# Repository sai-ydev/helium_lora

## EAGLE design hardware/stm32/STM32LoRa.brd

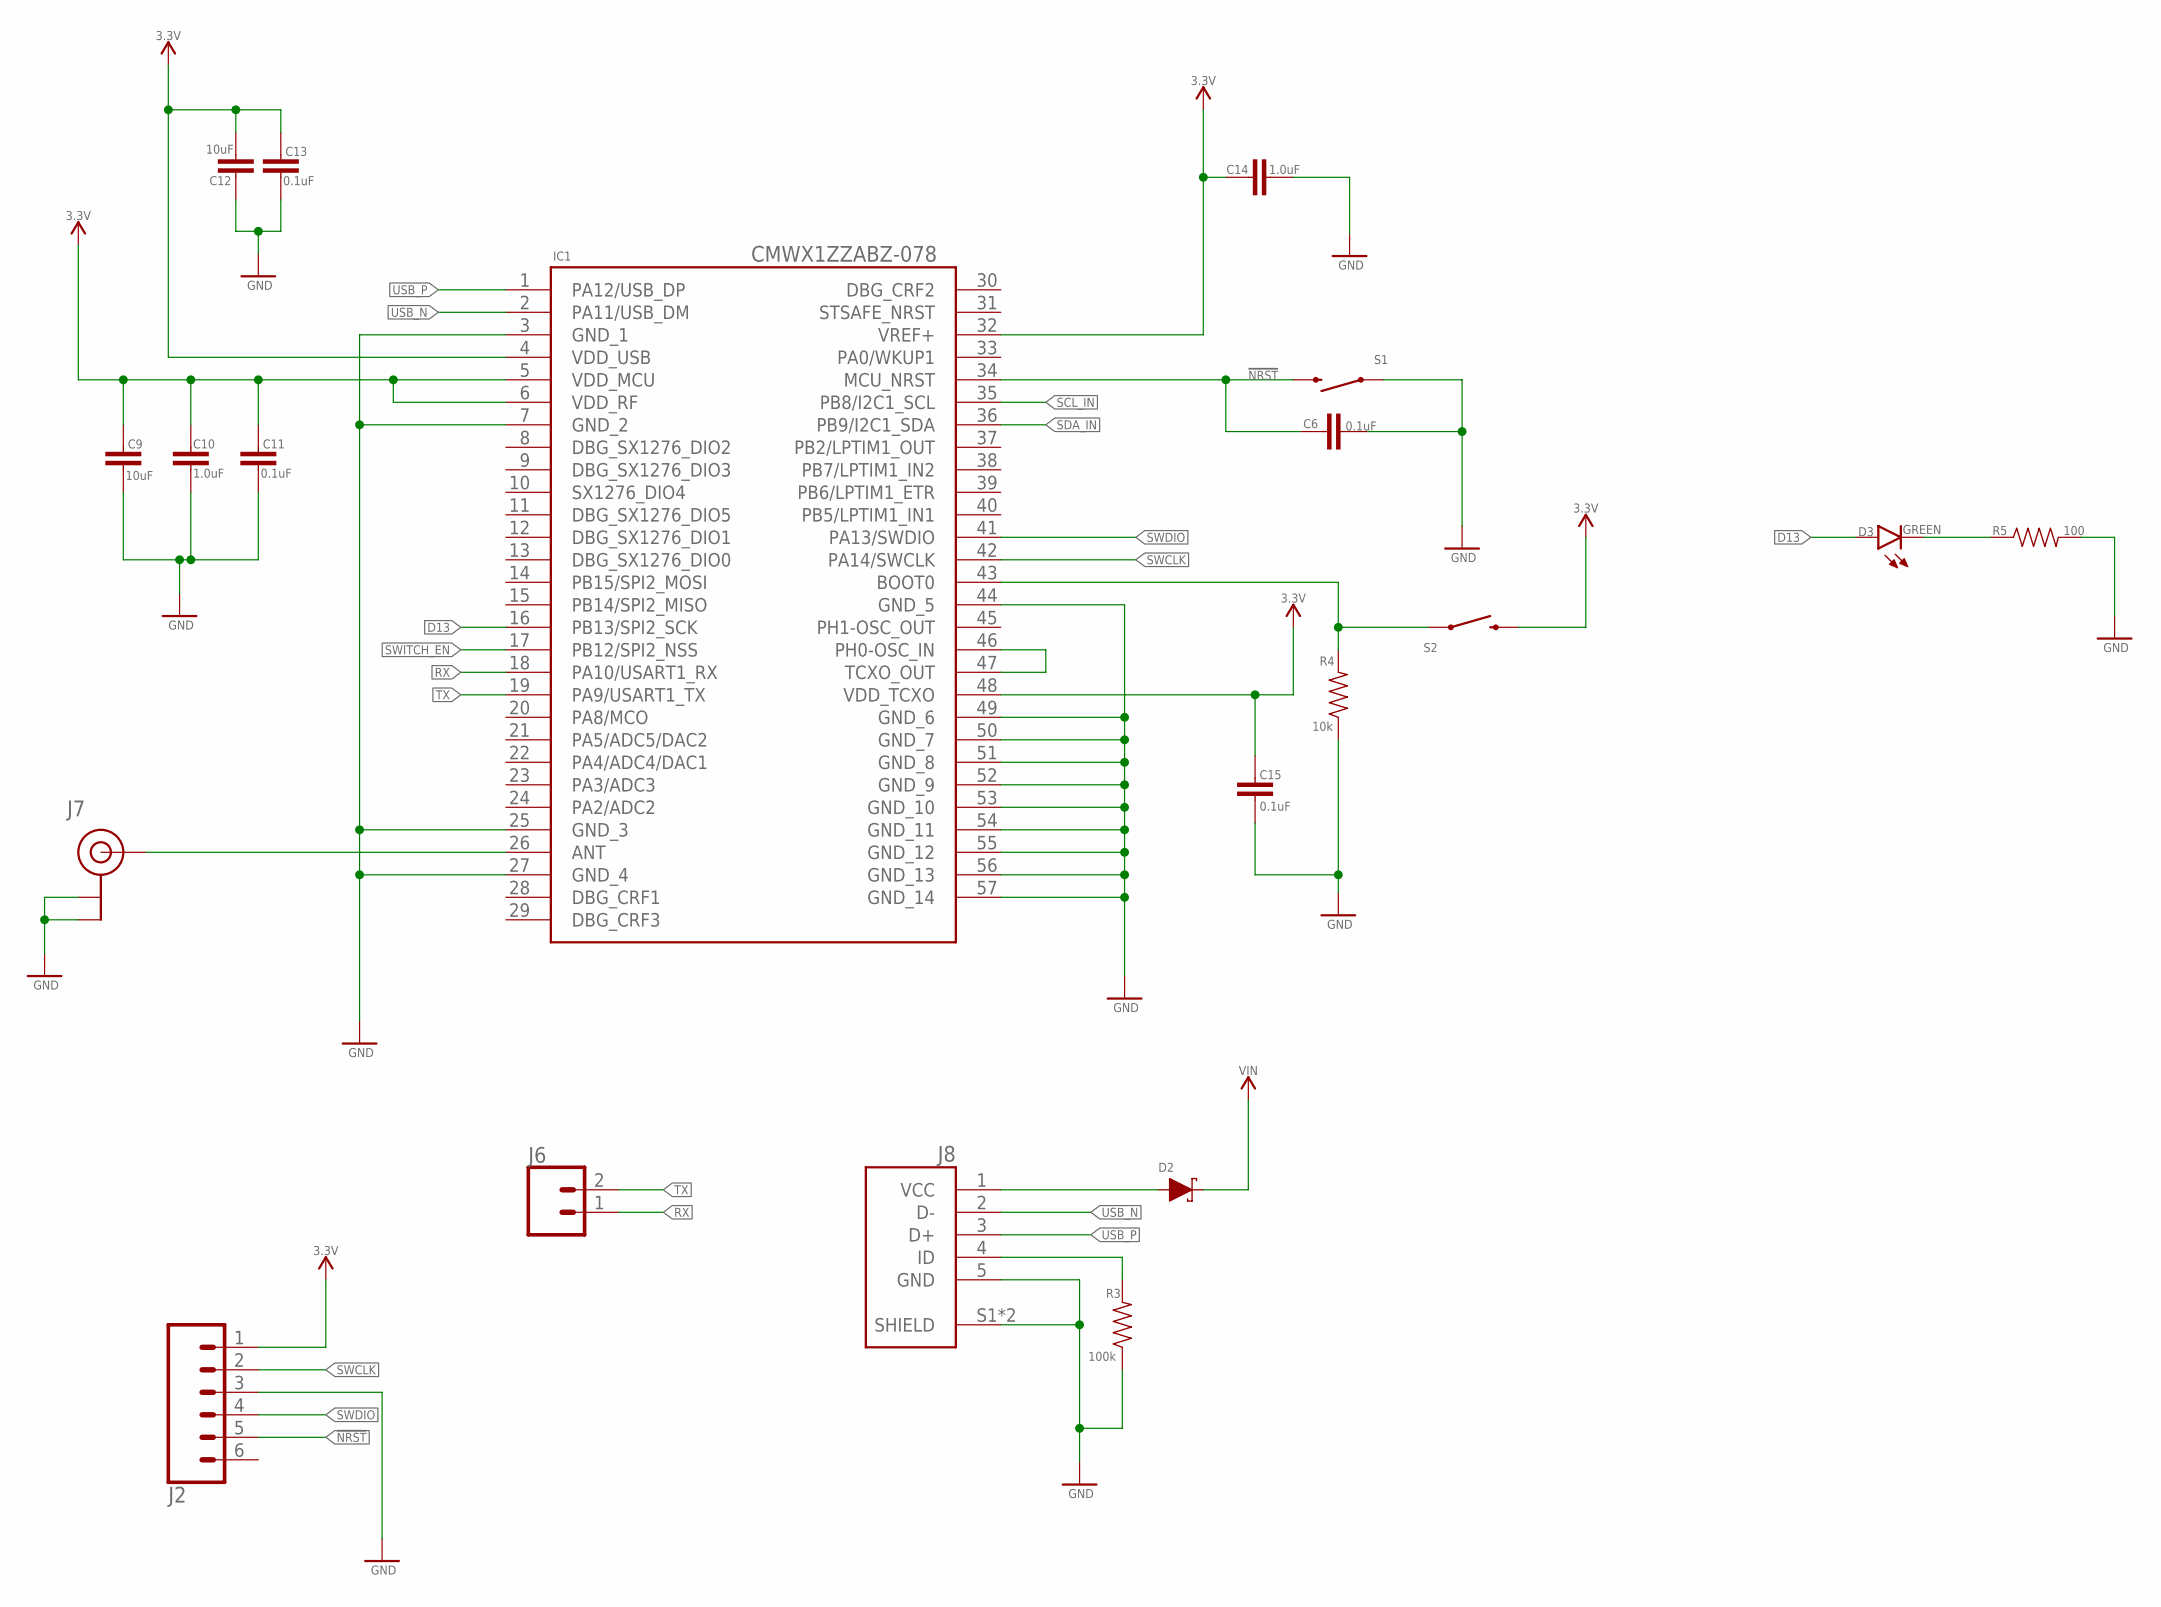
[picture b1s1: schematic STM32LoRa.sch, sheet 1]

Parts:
C6, C11, C13, C15: 0.1uF; 0603
C9, C12: 10uF; 0603
C10, C14: 1.0uF; 0603
D2: 120mA/40V/370mV; SOD-523
D3: GREEN; LED-0603
IC1: CMWX1ZZABZ-078
J2: CONN_06LONGPADS; 1X06_LONGPADS
J6: CONN_02; 1X02
J7: U.FL
J8: USB3131-30-0230-A_REVB; GCT_USB3131-30-0230-A_REVB
R3: 100k; 0603
R4: 10k; 0603
R5: 100; 0603
S1, S2: MOMENTARY-SWITCH-SPST-SMD-4.6X2.8MM; TACTILE_SWITCH_SMD_4.6X2.8MM

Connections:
3.3V: C9.1, C10.1, C11.1, C12.2, C13.1, C14.1, C15.2, IC1.4 (VDD_USB), IC1.5 (VDD_MCU), IC1.6 (VDD_RF), IC1.32 (VREF+), IC1.48 (VDD_TCXO), J2.1, S2.3 (2), S2.4 (2); also elsewhere on the board
!NRST: C6.1, IC1.34 (MCU_NRST), J2.5, S1.3 (2), S1.4 (2)
D13: D3.A, IC1.16 (PB13/SPI2_SCK)
GND: C6.2, C9.2, C10.2, C11.2, C12.1, C13.2, C14.2, C15.1, IC1.3 (GND_1), IC1.7 (GND_2), IC1.25 (GND_3), IC1.27 (GND_4), IC1.44 (GND_5), IC1.49 (GND_6), IC1.50 (GND_7), IC1.51 (GND_8), IC1.52 (GND_9), IC1.53 (GND_10), IC1.54 (GND_11), IC1.55 (GND_12), IC1.56 (GND_13), IC1.57 (GND_14), J2.3, J7.1 (GND), J7.2 (GND), J8.5 (GND), J8.S1 (SHIELD), J8.S2 (SHIELD), R3.1, R4.1, R5.2, S1.1, S1.2 (1); also elsewhere on the board
unnamed: IC1.43 (BOOT0), R4.2, S2.1, S2.2 (1)
unnamed: IC1.46 (PH0-OSC_IN), IC1.47 (TCXO_OUT)
unnamed: IC1.26 (ANT), J7.FEED (SIGNAL)
unnamed: D3.C, R5.1
unnamed: J8.4 (ID), R3.2
unnamed: D2.A, J8.1 (VCC)
RX: IC1.18 (PA10/USART1_RX), J6.1
SCL_IN: IC1.35 (PB8/I2C1_SCL); also elsewhere on the board
SDA_IN: IC1.36 (PB9/I2C1_SDA); also elsewhere on the board
SWCLK: IC1.42 (PA14/SWCLK), J2.2
SWDIO: IC1.41 (PA13/SWDIO), J2.4
SWITCH_EN: IC1.17 (PB12/SPI2_NSS); also elsewhere on the board
TX: IC1.19 (PA9/USART1_TX), J6.2
USB_N: IC1.2 (PA11/USB_DM), J8.2 (D-)
USB_P: IC1.1 (PA12/USB_DP), J8.3 (D+)
VIN: D2.C; also elsewhere on the board

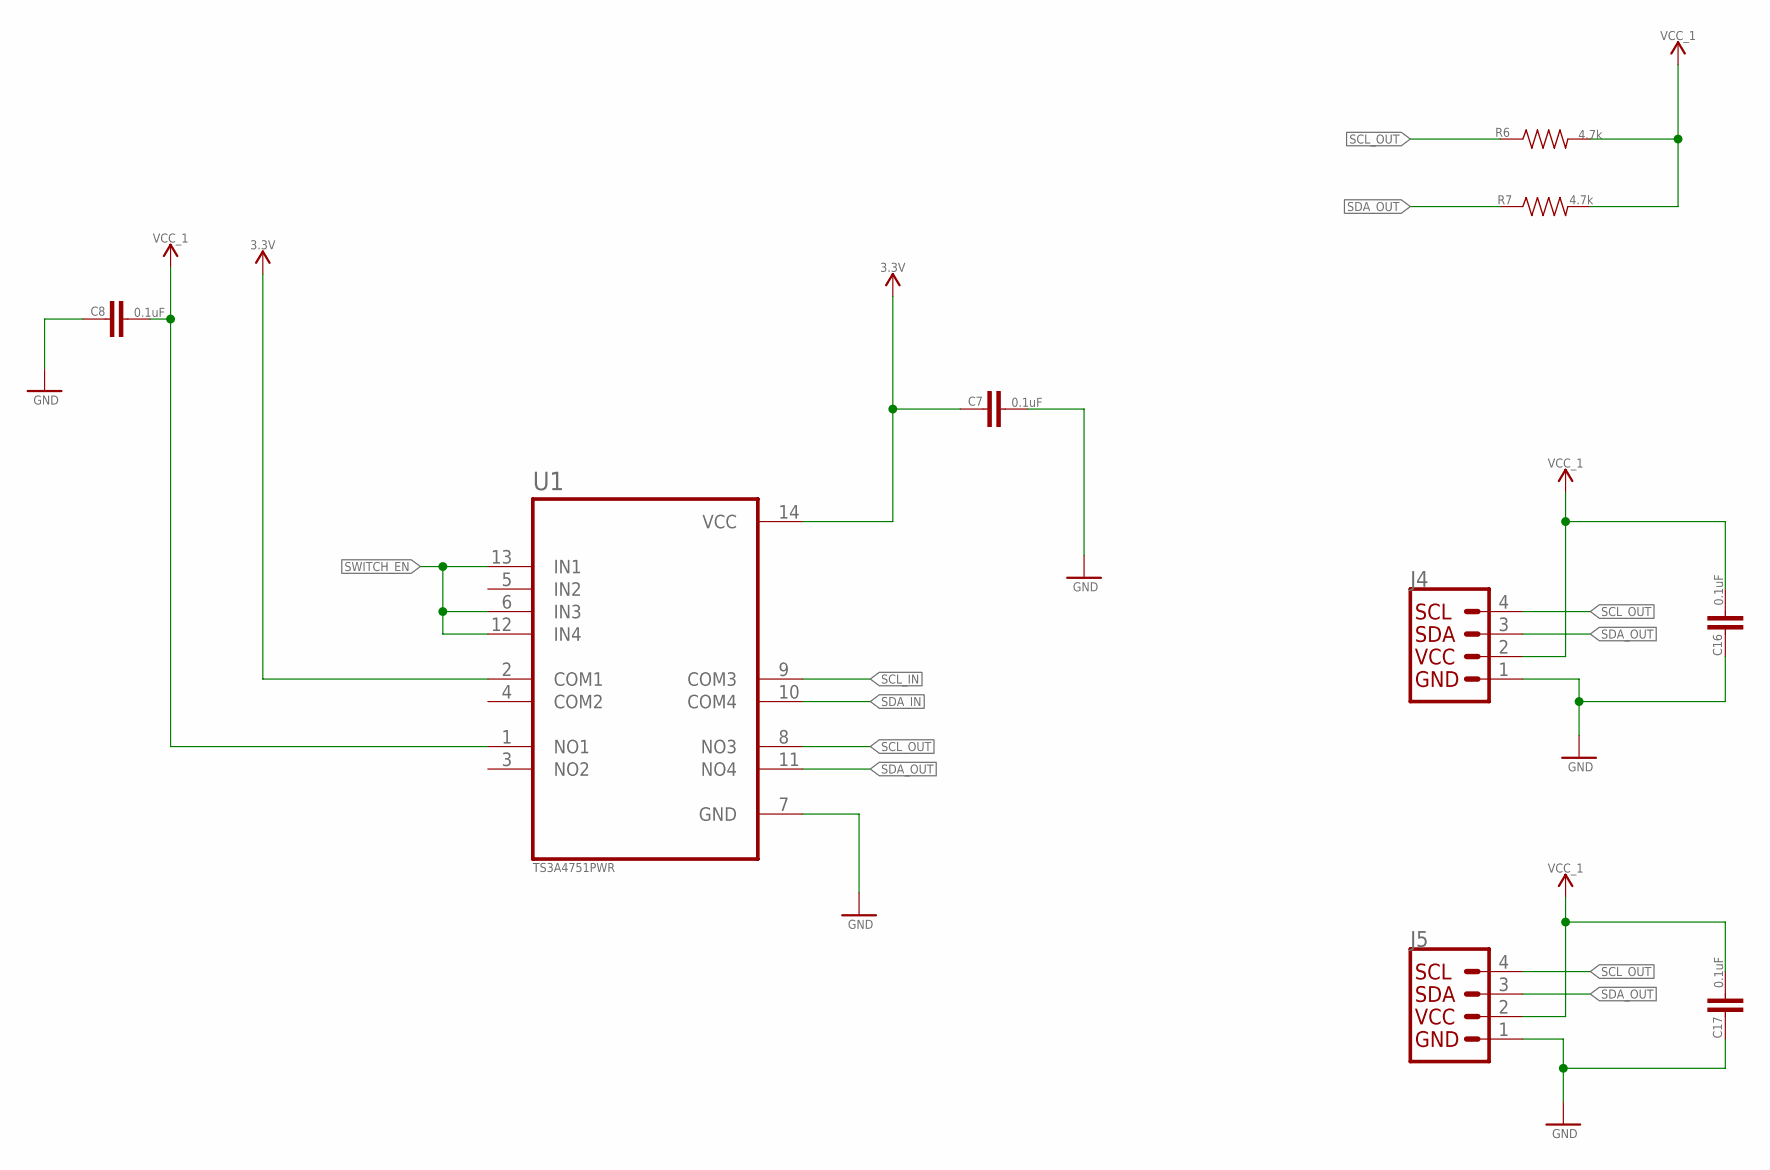
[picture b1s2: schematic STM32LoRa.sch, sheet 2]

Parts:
C7, C8, C16, C17: 0.1uF; 0603
J4: Qwiic Right Angle; 1X04_1MM_RA
J5: I2C_STANDARD; 1X04
R6, R7: 4.7k; 0603
U1: TS3A4751PWR; SOP65P640X120-14N

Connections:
3.3V: C7.1, U1.2 (COM1), U1.14 (VCC); also elsewhere on the board
GND: C7.2, C8.1, C16.1, C17.1, J4.1, J5.1, U1.7 (GND); also elsewhere on the board
SCL_IN: U1.9 (COM3); also elsewhere on the board
SCL_OUT: J4.4, J5.4, R6.1, U1.8 (NO3)
SDA_IN: U1.10 (COM4); also elsewhere on the board
SDA_OUT: J4.3, J5.3, R7.1, U1.11 (NO4)
SWITCH_EN: U1.6 (IN3), U1.12 (IN4), U1.13 (IN1); also elsewhere on the board
VCC_1: C8.2, C16.2, C17.2, J4.2, J5.2, R6.2, R7.2, U1.1 (NO1)

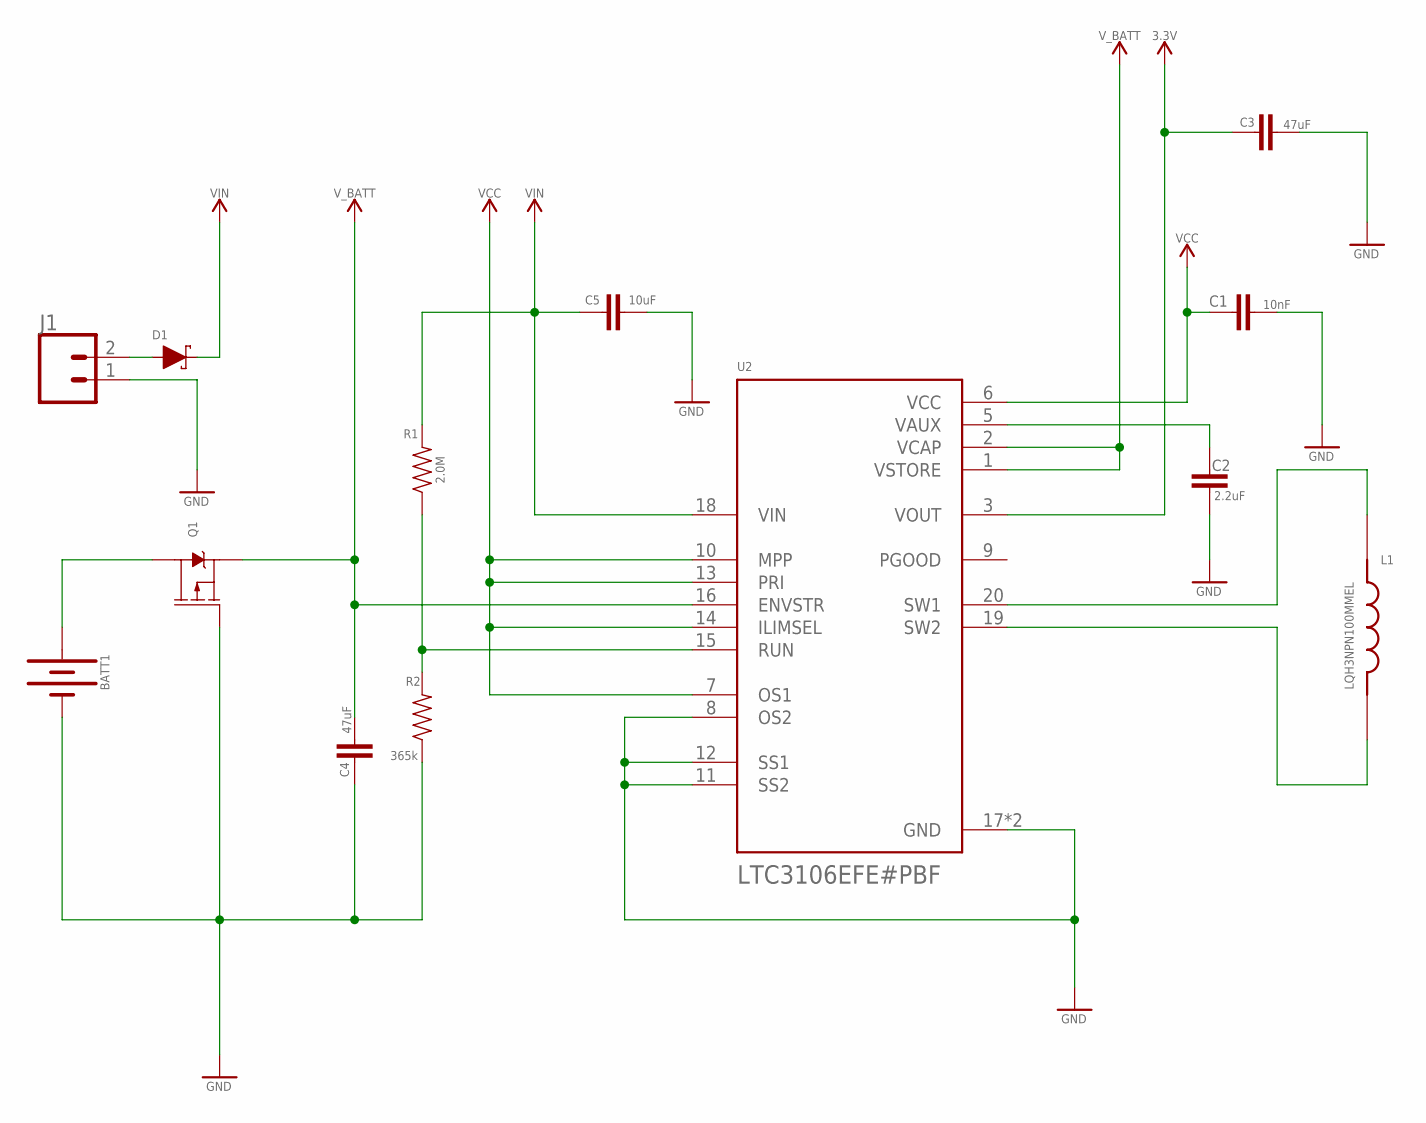
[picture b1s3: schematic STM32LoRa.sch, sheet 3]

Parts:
BATT1: KEYSTONE_54KEYSTONE_2; KEYSTONE_V2
C1: 10nF; 0603
C2: 2.2uF; 0603
C3, C4: 47uF; 0603
C5: 10uF; 0603
D1: 120mA/40V/370mV; SOD-523
J1: CONN_023.5MM; SCREWTERMINAL-3.5MM-2
L1: LQH3NPN100MMEL; IND_LQH3NPN100MMEL
Q1: 2.5A/30V/105mΩ; SOT23-3
R1: 2.0M; 0603
R2: 365k; 0603
U2: LTC3106EFE#PBF; SOP65P640X120-21N

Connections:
3.3V: C3.1, U2.3 (VOUT); also elsewhere on the board
GND: BATT1.P$4 (-), BATT1.P$5 (-), BATT1.P$6 (-), C1.2, C2.2, C3.2, C4.1, C5.2, J1.1, Q1.1 (G), R2.1, U2.8 (OS2), U2.11 (SS2), U2.12 (SS1), U2.17 (GND), U2.21 (GND); also elsewhere on the board
unnamed: L1.1, U2.20 (SW1)
unnamed: L1.2, U2.19 (SW2)
unnamed: C2.1, U2.5 (VAUX)
unnamed: BATT1.P$1 (+), BATT1.P$2 (+), BATT1.P$3 (+), Q1.3 (D)
unnamed: R1.1, R2.2, U2.15 (RUN)
unnamed: D1.A, J1.2
VCC: C1.1, U2.6 (VCC), U2.7 (OS1), U2.10 (MPP), U2.13 (PRI), U2.14 (ILIMSEL)
VIN: C5.1, D1.C, R1.2, U2.18 (VIN); also elsewhere on the board
V_BATT: C4.2, Q1.2 (S), U2.1 (VSTORE), U2.2 (VCAP), U2.16 (ENVSTR)

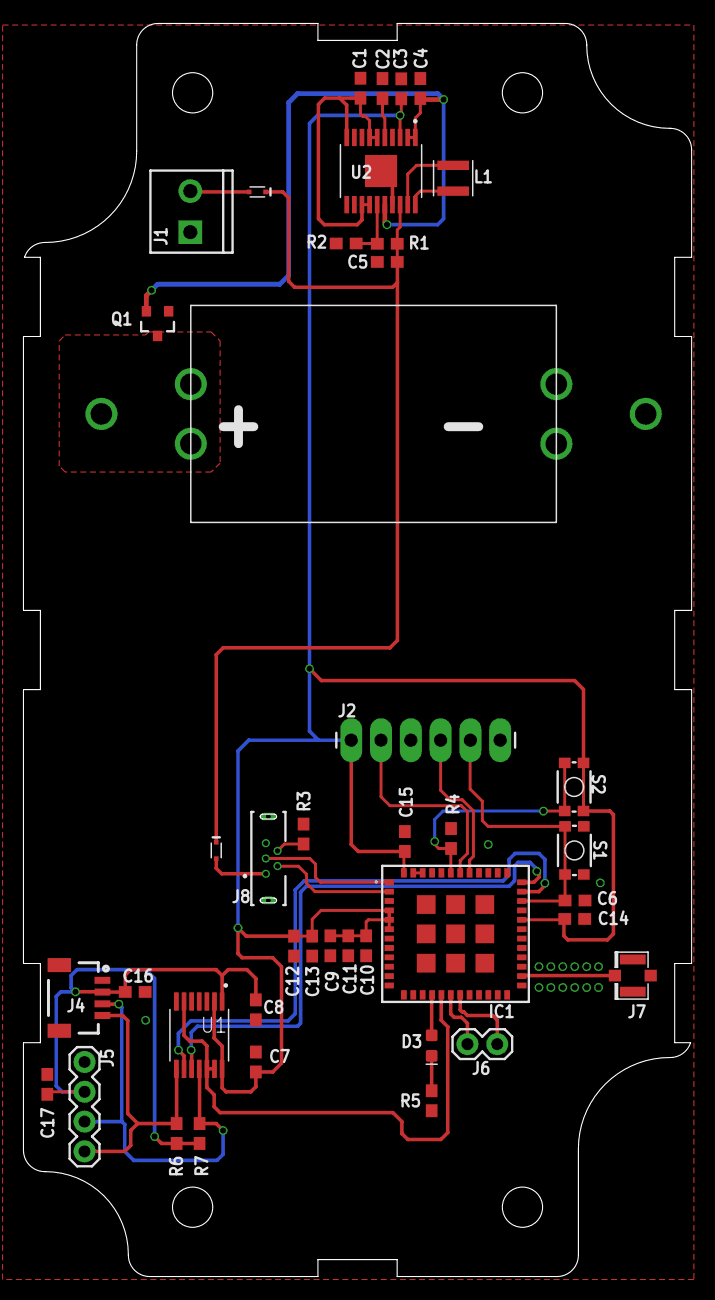
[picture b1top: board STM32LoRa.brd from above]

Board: 2 copper layers, 57.0 x 106.8 mm, 42 parts (0 on the bottom side), 31 nets.

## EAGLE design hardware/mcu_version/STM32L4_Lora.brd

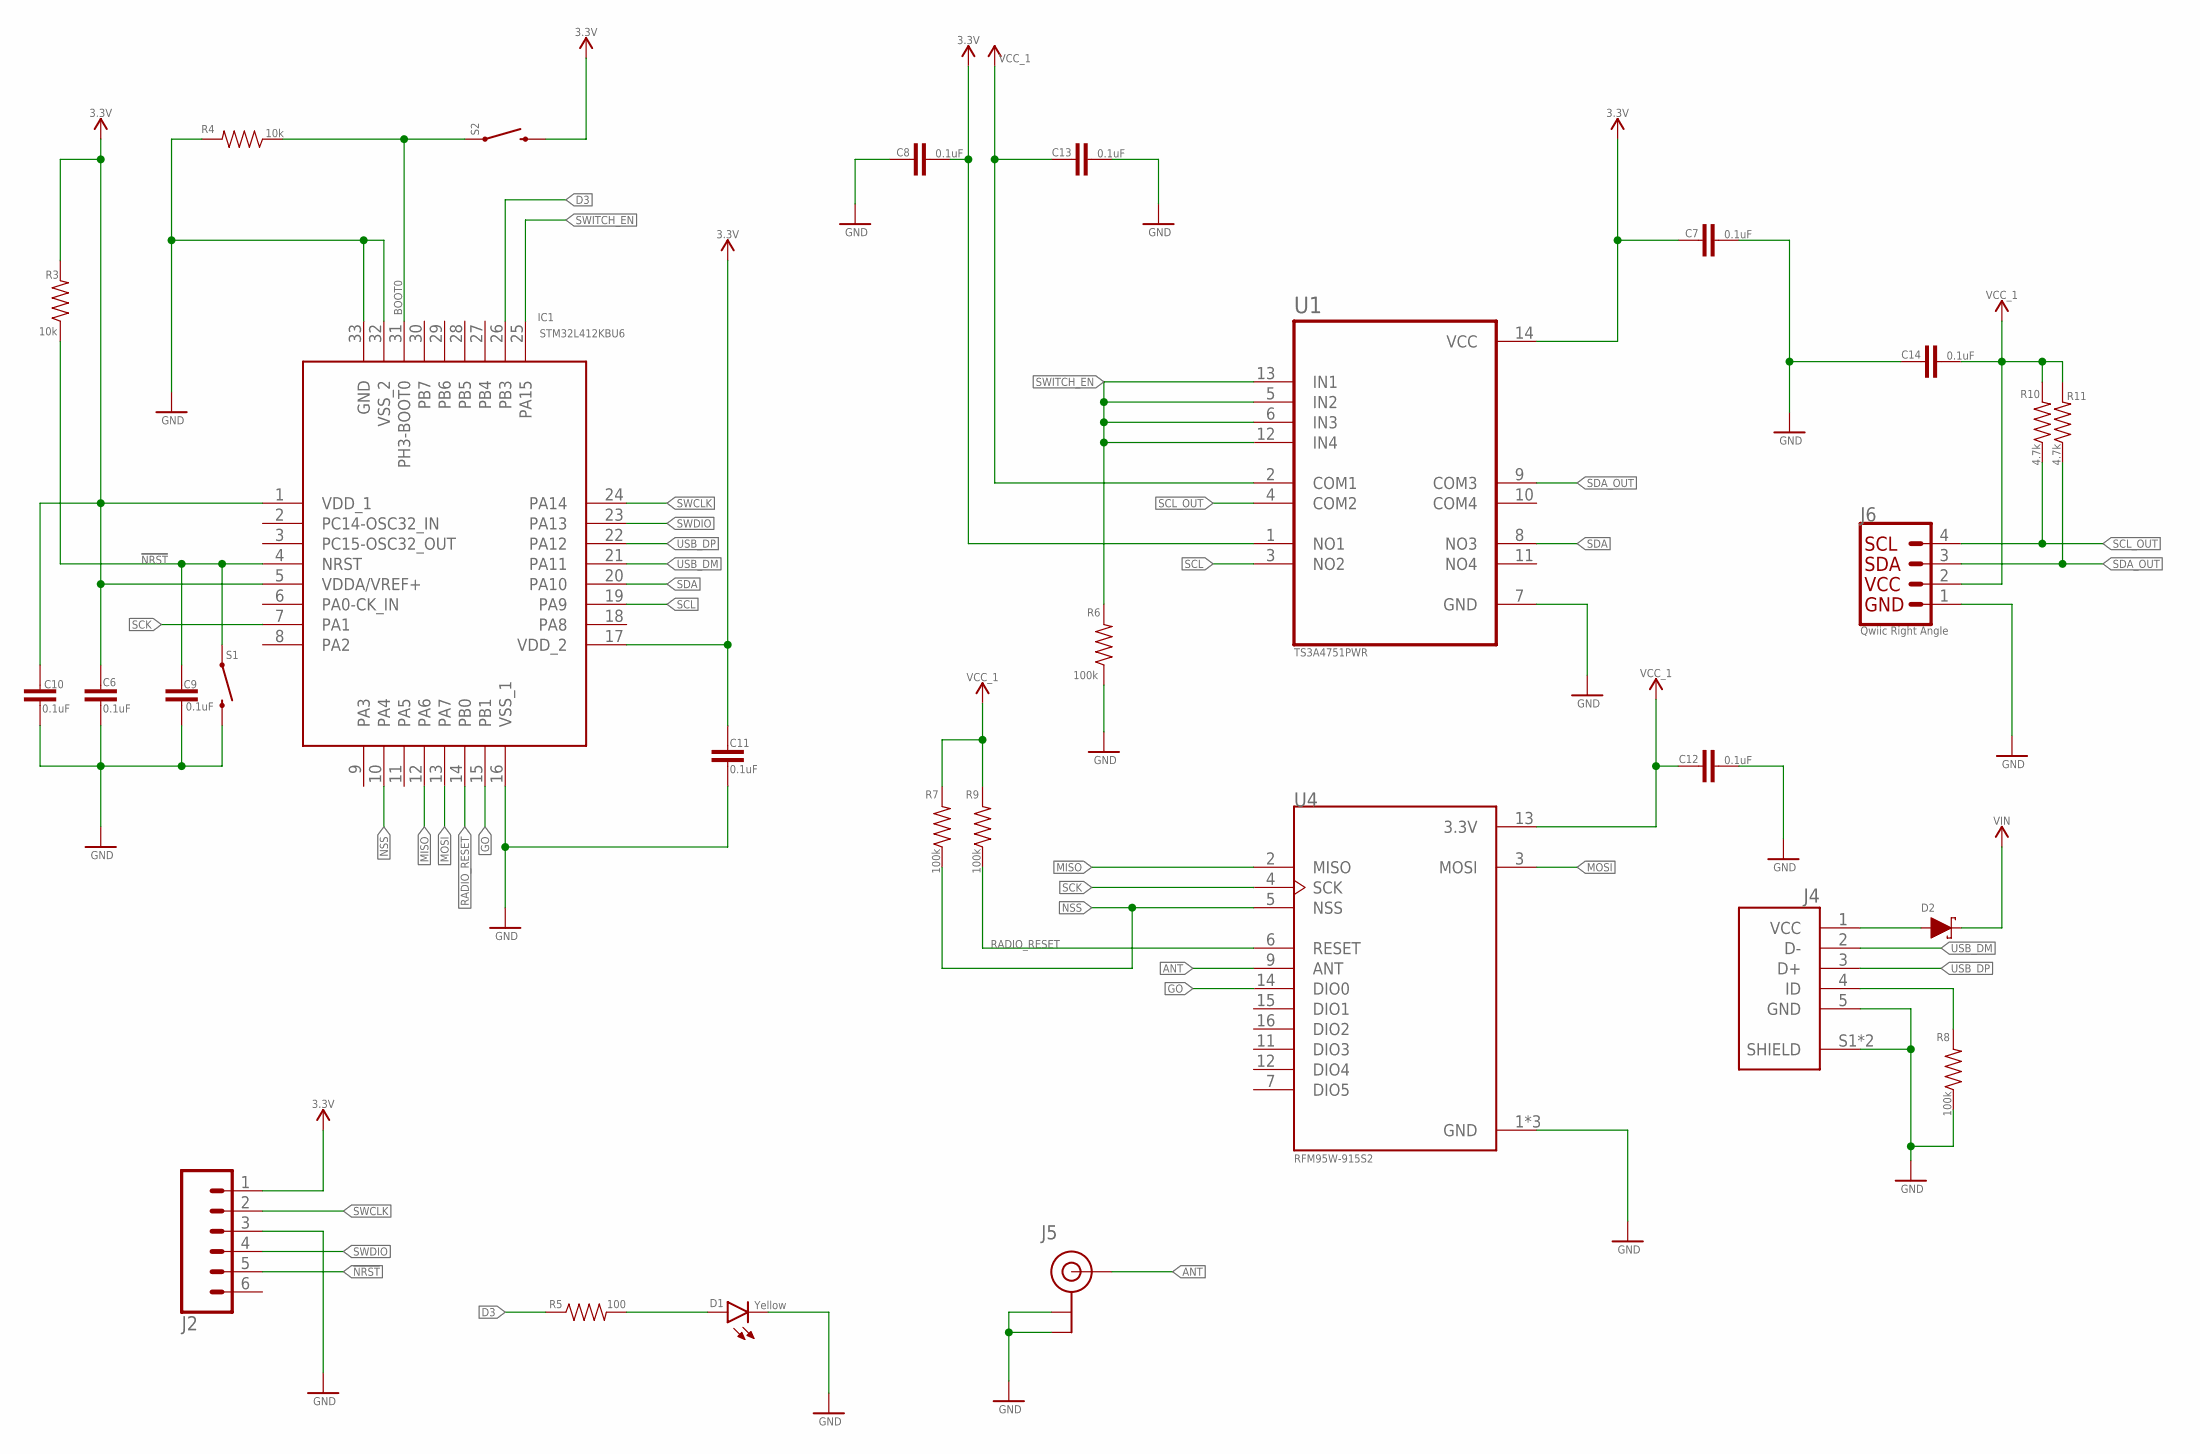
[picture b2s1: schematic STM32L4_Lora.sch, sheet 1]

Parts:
C6, C7, C8, C9, C10, C11, C12, C13, C14: 0.1uF; 0603
D1: Yellow; LED-0603
D2: 120mA/40V/370mV; SOD-523
IC1: STM32L412KBU6; QFN50P500X500X60-33N
J2: CONN_06LOCK_LONGPADS; 1X06_LOCK_LONGPADS
J4: USB3131-30-0230-A_REVB; GCT_USB3131-30-0230-A_REVB
J5: U.FL
J6: Qwiic Right Angle; 1X04_1MM_RA
R3, R4: 10k; 0603
R5: 100; 0603
R6, R7, R8, R9: 100k; 0603
R10, R11: 4.7k; 0603
S1, S2: MOMENTARY-SWITCH-SPST-SMD-4.6X2.8MM; TACTILE_SWITCH_SMD_4.6X2.8MM
U1: TS3A4751PWR; SOP65P640X120-14N
U4: RFM95W-915S2; XCVR_RFM95W-915S2

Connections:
3.3V: C6.1, C7.1, C8.2, C10.1, C11.1, IC1.1 (VDD_1), IC1.5 (VDDA/VREF+), IC1.17 (VDD_2), J2.1, R3.2, S2.3 (2), S2.4 (2), U1.1 (NO1), U1.14 (VCC); also elsewhere on the board
!NRST: C9.1, IC1.4 (NRST), J2.5, R3.1, S1.1, S1.2 (1)
ANT: J5.FEED (SIGNAL), U4.9 (ANT)
BOOT0: IC1.31 (PH3-BOOT0), R4.1, S2.1, S2.2 (1)
D3: IC1.26 (PB3), R5.1
GND: C6.2, C7.2, C8.1, C9.2, C10.2, C11.2, C12.2, C13.2, C14.1, D1.C, IC1.16 (VSS_1), IC1.32 (VSS_2), IC1.33 (GND), J2.3, J4.5 (GND), J4.S1 (SHIELD), J4.S2 (SHIELD), J5.1 (GND), J5.2 (GND), J6.1, R4.2, R6.1, R8.1, S1.3 (2), S1.4 (2), U1.7 (GND), U4.1 (GND), U4.8 (GND), U4.10 (GND); also elsewhere on the board
GO: IC1.15 (PB1), U4.14 (DIO0)
MISO: IC1.12 (PA6), U4.2 (MISO)
MOSI: IC1.13 (PA7), U4.3 (MOSI)
unnamed: D1.A, R5.2
unnamed: J4.4 (ID), R8.2
unnamed: D2.A, J4.1 (VCC)
NSS: IC1.10 (PA4), R7.1, U4.5 (NSS)
RADIO_RESET: IC1.14 (PB0), R9.1, U4.6 (RESET)
SCK: IC1.7 (PA1), U4.4 (SCK)
SCL: IC1.19 (PA9), U1.3 (NO2)
SCL_OUT: J6.4, R10.1, U1.4 (COM2)
SDA: IC1.20 (PA10), U1.8 (NO3)
SDA_OUT: J6.3, R11.1, U1.9 (COM3)
SWCLK: IC1.24 (PA14), J2.2
SWDIO: IC1.23 (PA13), J2.4
SWITCH_EN: IC1.25 (PA15), R6.2, U1.5 (IN2), U1.6 (IN3), U1.12 (IN4), U1.13 (IN1)
USB_DM: IC1.21 (PA11), J4.2 (D-)
USB_DP: IC1.22 (PA12), J4.3 (D+)
VCC_1: C12.1, C13.1, C14.2, J6.2, R7.2, R9.2, R10.2, R11.2, U1.2 (COM1), U4.13 (3.3V)
VIN: D2.C; also elsewhere on the board

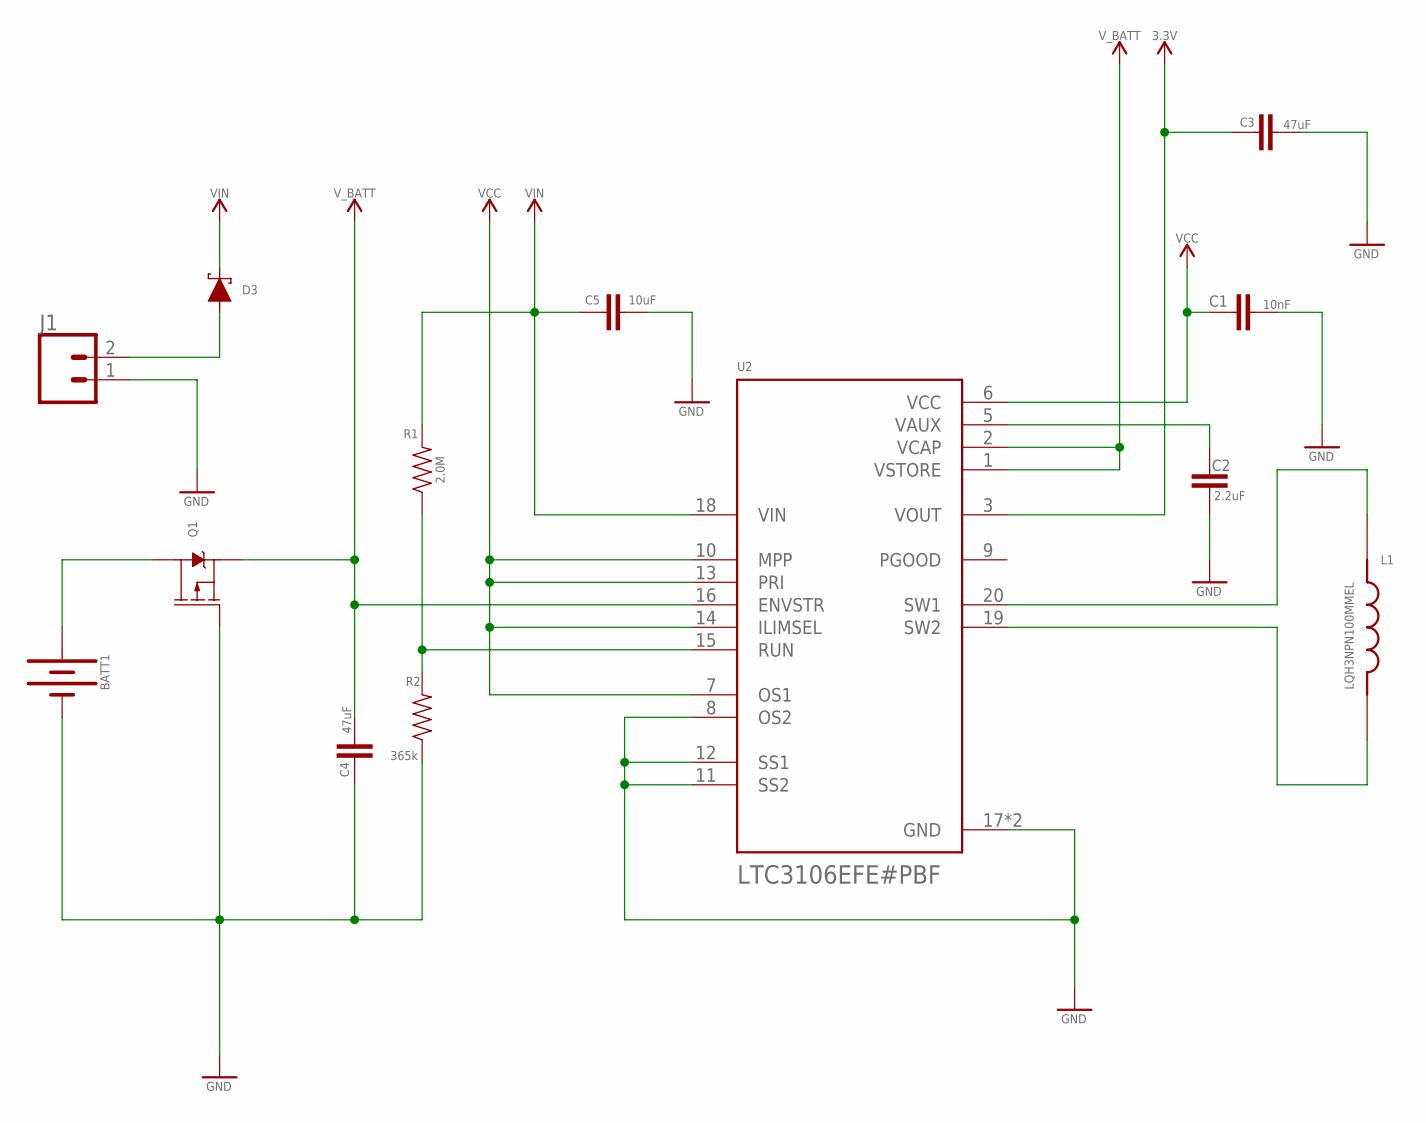
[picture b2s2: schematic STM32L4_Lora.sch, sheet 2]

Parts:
BATT1: KEYSTONE_54KEYSTONE_2; KEYSTONE_V2
C1: 10nF; 0603
C2: 2.2uF; 0603
C3, C4: 47uF; 0603
C5: 10uF; 0603
D3: 120mA/40V/370mV; SOD-523
J1: CONN_023.5MM; SCREWTERMINAL-3.5MM-2
L1: LQH3NPN100MMEL; IND_LQH3NPN100MMEL
Q1: 2.5A/30V/105mΩ; SOT23-3
R1: 2.0M; 0603
R2: 365k; 0603
U2: LTC3106EFE#PBF; SOP65P640X120-21N

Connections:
3.3V: C3.1, U2.3 (VOUT); also elsewhere on the board
GND: BATT1.P$4 (-), BATT1.P$5 (-), BATT1.P$6 (-), C1.2, C2.2, C3.2, C4.1, C5.2, J1.1, Q1.1 (G), R2.1, U2.8 (OS2), U2.11 (SS2), U2.12 (SS1), U2.17 (GND), U2.21 (GND); also elsewhere on the board
unnamed: L1.1, U2.20 (SW1)
unnamed: L1.2, U2.19 (SW2)
unnamed: C2.1, U2.5 (VAUX)
unnamed: BATT1.P$1 (+), BATT1.P$2 (+), BATT1.P$3 (+), Q1.3 (D)
unnamed: R1.1, R2.2, U2.15 (RUN)
unnamed: D3.A, J1.2
VCC: C1.1, U2.6 (VCC), U2.7 (OS1), U2.10 (MPP), U2.13 (PRI), U2.14 (ILIMSEL)
VIN: C5.1, D3.C, R1.2, U2.18 (VIN); also elsewhere on the board
V_BATT: C4.2, Q1.2 (S), U2.1 (VSTORE), U2.2 (VCAP), U2.16 (ENVSTR)

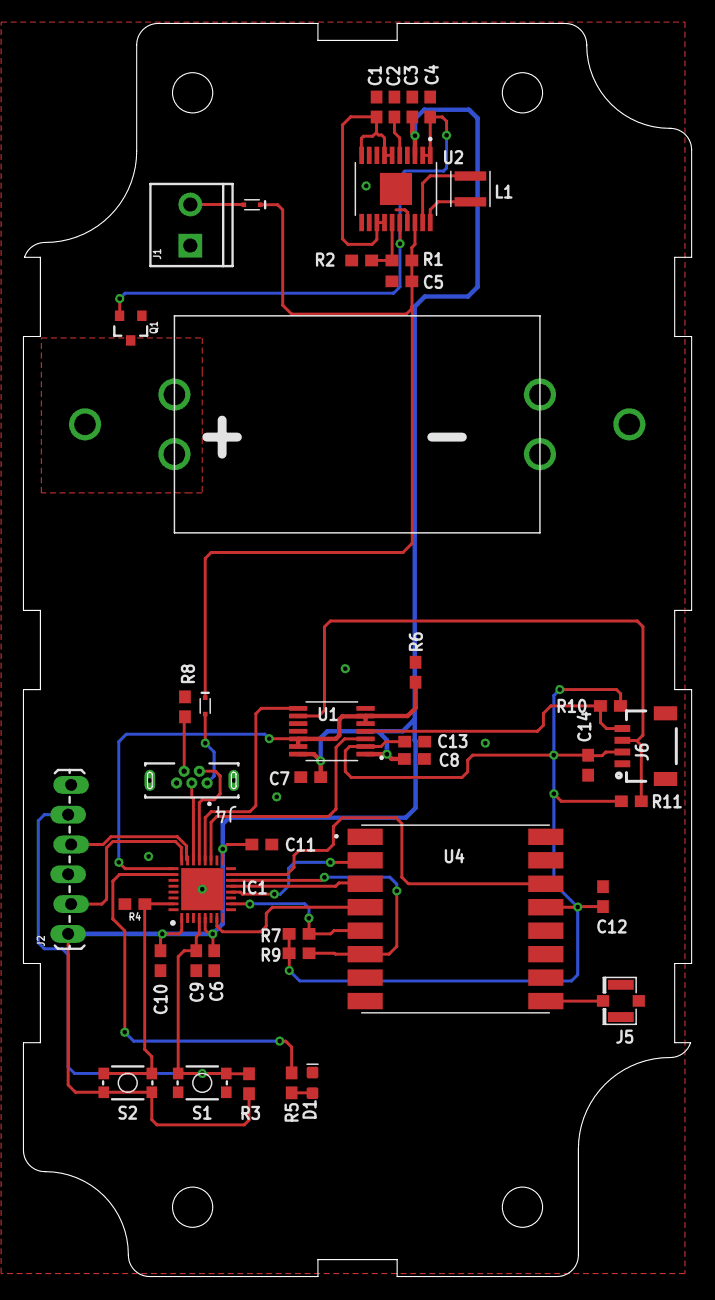
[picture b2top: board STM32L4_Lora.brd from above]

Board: 2 copper layers, 57.0 x 106.8 mm, 42 parts (0 on the bottom side), 34 nets.

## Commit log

2020-07-31 Schematic check-in
2020-08-03 Check in
2020-08-05 File check in
2020-08-06 gitignore changes
2020-08-14 STM32L4 design checkin

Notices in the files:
parts and their libraries:
SparkFun-Capacitors: Licensing: Creative Commons ShareAlike 4.0 International - https://creativecommons.org/licenses/by-sa/4.0
